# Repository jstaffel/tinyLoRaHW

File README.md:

# tinyLoRaHW
Hardware files of the tinyLoRa, a board that uses Rapsberry Pi's RP2040 microcontroller for LoRaWAN communication.
The board was designed in KiCad

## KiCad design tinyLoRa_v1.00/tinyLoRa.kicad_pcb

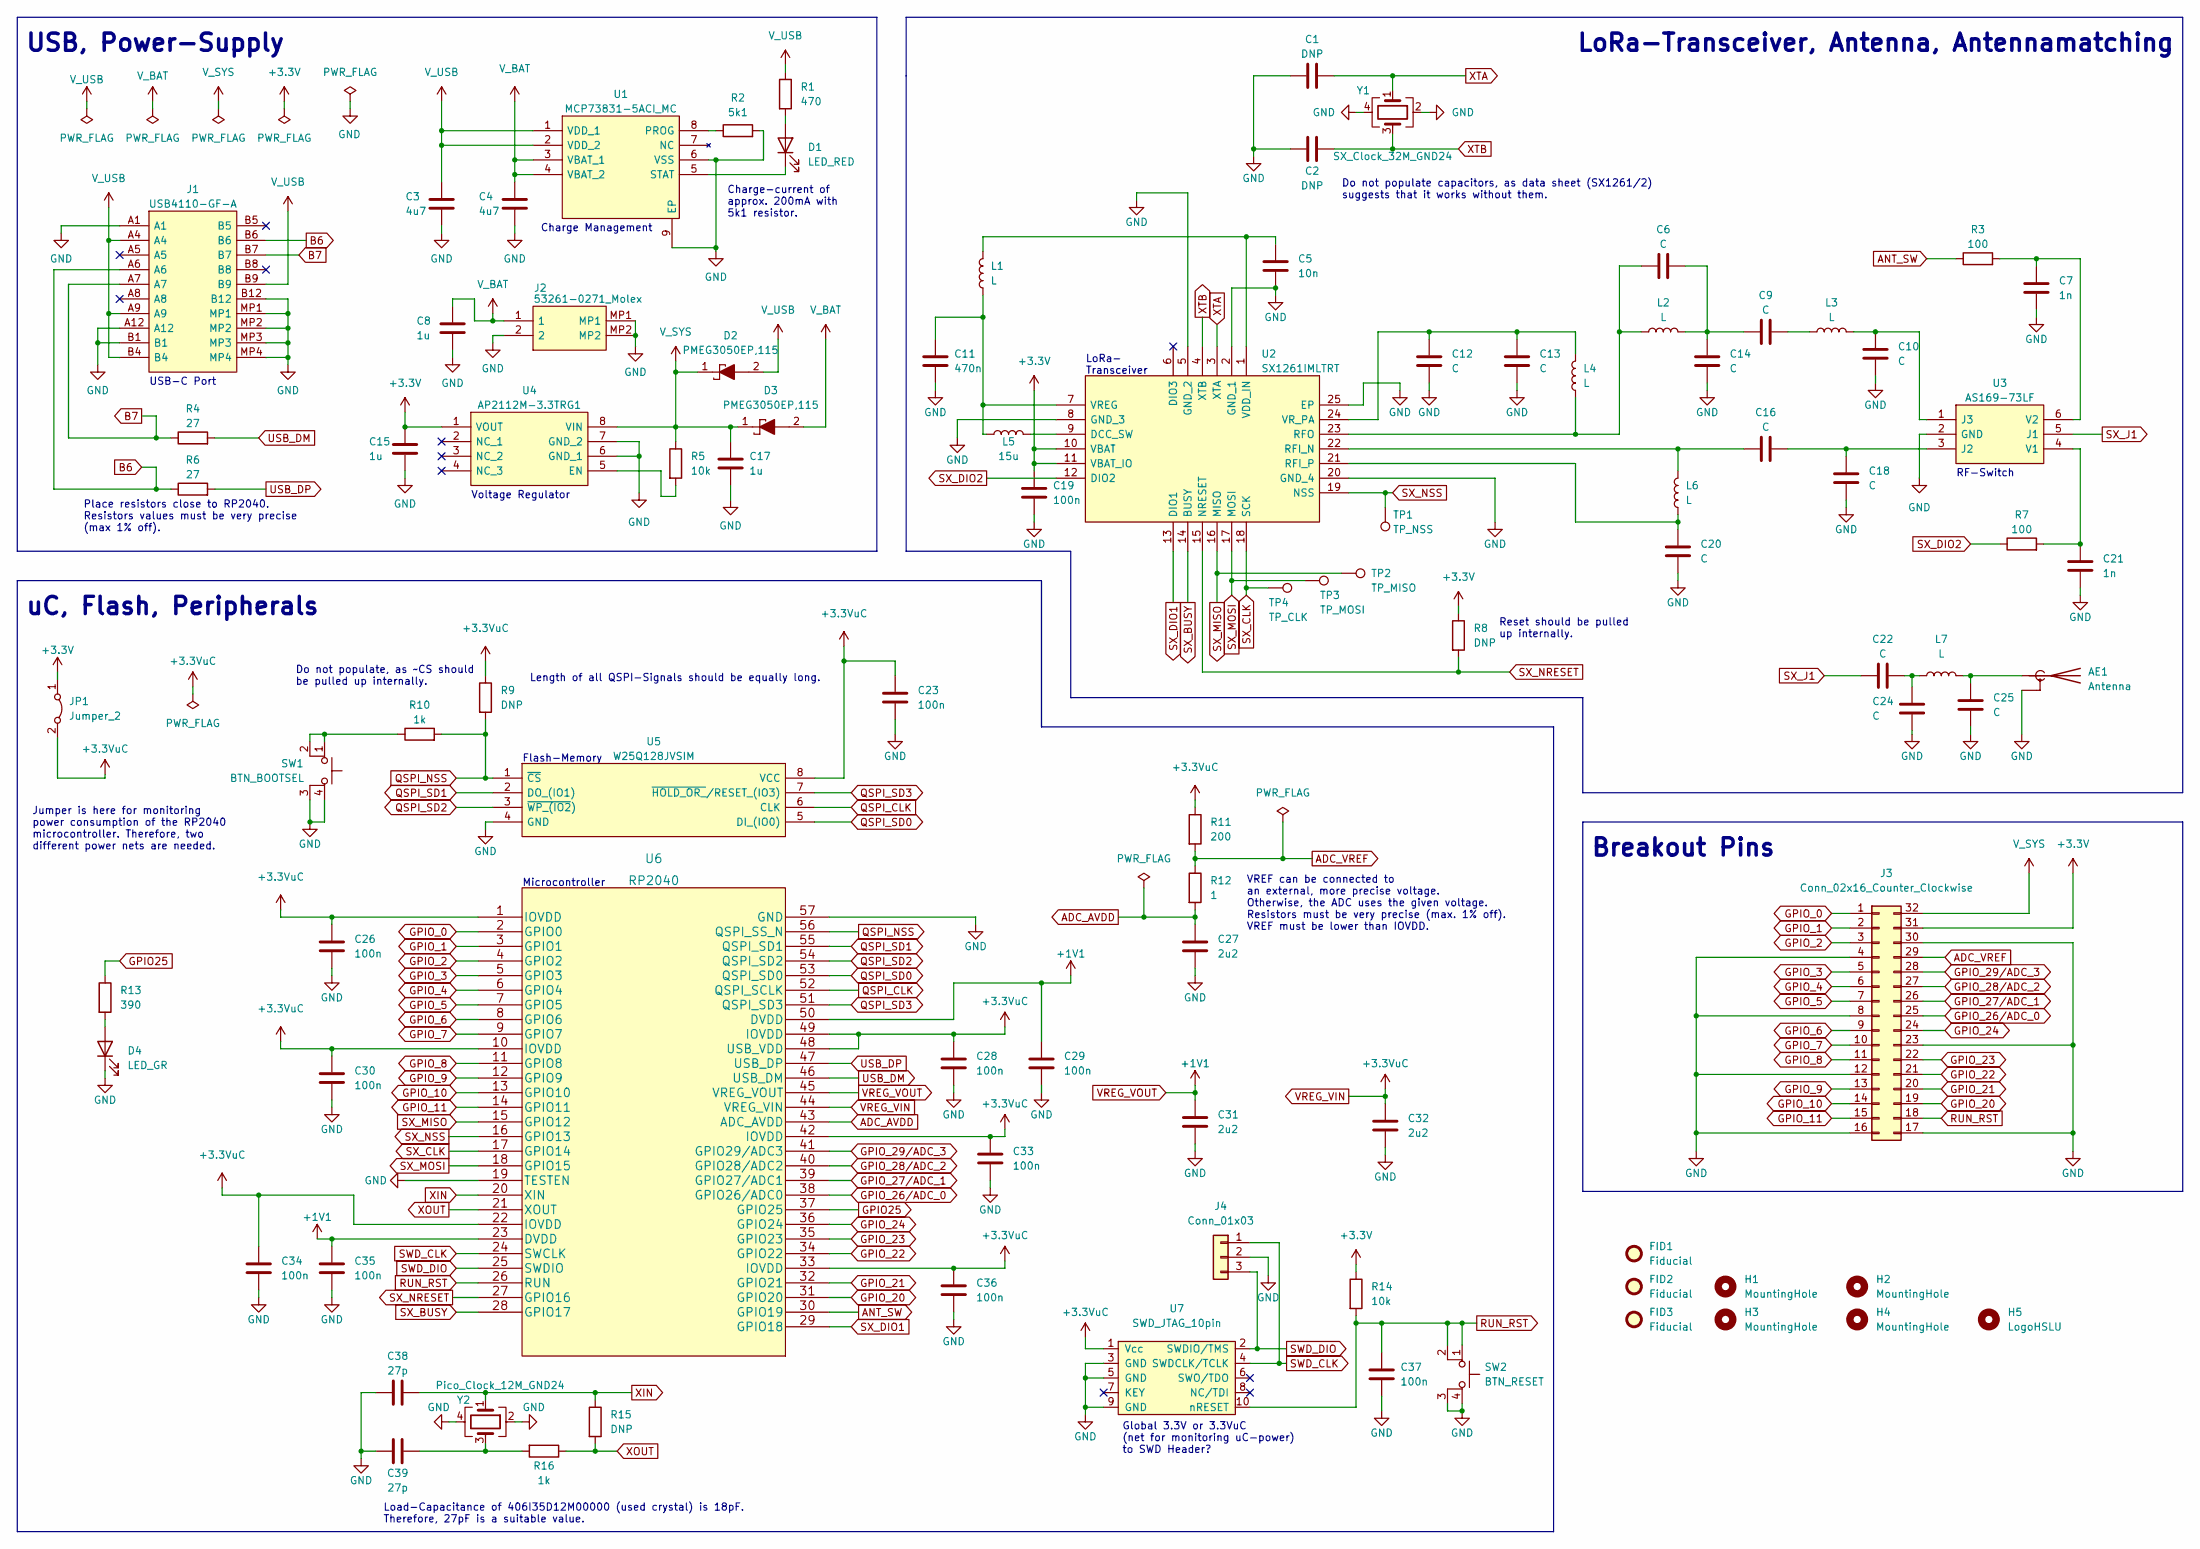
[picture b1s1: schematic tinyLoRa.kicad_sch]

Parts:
AE1: Antenna; antenna_connector
C1, C2: DNP; R_0603_1608Metric
C3, C4: 4u7; R_0603_1608Metric
C5: 10n; R_0603_1608Metric
C6, C9, C10, C12, C13, C14, C16, C18, C20, C22, C24, C25: C; R_0402_1005Metric
C7, C21: 1n; R_0603_1608Metric
C8, C15, C17: 1u; R_0603_1608Metric
C11: 470n; R_0603_1608Metric
C19, C23, C37: 100n; R_0603_1608Metric
C26, C28, C29, C30, C33, C34, C35, C36: 100n; R_0402_1005Metric
C27, C31, C32: 2u2; R_0402_1005Metric
C38, C39: 27p; R_0603_1608Metric
D1: LED_RED; R_0603_1608Metric
D2, D3: PMEG3050EP,115; PMEG3050EP115; Mouser Part Number 771-PMEG3050EP115
D4: LED_GR; R_0603_1608Metric
FID1, FID2, FID3: Fiducial; Fiducial_1mm_Dia_2.54mm_Outer_CopperTop
H1, H2, H3, H4: MountingHole; MountingHole_2.7mm_M2.5_LargeMask
H5: LogoHSLU; hslu_logo_new
J1: USB4110-GF-A; USB4110GFA; Mouser Part Number 640-USB4110-GF-A
J2: 53261-0271_Molex; 532610271_Molex; Mouser Part Number 538-53261-0271
J3: Conn_02x16_Counter_Clockwise; PinHeader_tinyLoRa
J4: Conn_01x03; PinSocket_1x03_P2.54mm_Vertical
JP1: Jumper_2; PinSocket_1x02_P2.54mm_Vertical
L1: L; R_0603_1608Metric
L2, L3, L4, L6, L7: L; R_0402_1005Metric
L5: 15u; R_0603_1608Metric
R1: 470; R_0603_1608Metric
R2: 5k1; R_0603_1608Metric
R3, R7: 100; R_0603_1608Metric
R4, R6: 27; R_0603_1608Metric
R5, R14: 10k; R_0603_1608Metric
R8, R9, R15: DNP; R_0603_1608Metric
R10, R16: 1k; R_0603_1608Metric
R11: 200; R_0603_1608Metric
R12: 1; R_0603_1608Metric
R13: 390; R_0603_1608Metric
SW1: BTN_BOOTSEL; 434123025826_BTN
SW2: BTN_RESET; 434123025826_BTN
TP1: TP_NSS; TestPoint_Pad_D1.0mm
TP2: TP_MISO; TestPoint_Pad_D1.0mm
TP3: TP_MOSI; TestPoint_Pad_D1.0mm
TP4: TP_CLK; TestPoint_Pad_D1.0mm
U1: MCP73831-5ACI_MC; SON50P300X200X100-9N-D; Mouser Part Number 579-MCP73831-5ACI/MC
U2: SX1261IMLTRT; QFN50P400X400X100-25N-D; Mouser Part Number 947-SX1261IMLTRT
U3: AS169-73LF; SOT95P270X145-6N; Mouser Part Number 873-AS169-73LF
U4: AP2112M-3.3TRG1; SOIC127P600X170-8N; Mouser Part Number 621-AP2112M-3.3TRG1
U5: W25Q128JVSIM; SOIC127P790X216-8N; Mouser Part Number 454-W25Q128JVSIM
U6: RP2040
U7: SWD_JTAG_10pin; SWD_Pin_Header_Straight_2x05_Pitch1.27mm
Y1: SX_Clock_32M_GND24; SX_Clock_GND24
Y2: Pico_Clock_12M_GND24; Pico_Clock_GND24

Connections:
+3V3: C15.1, C19.1, J3.31, JP1.1 (A), R8.1, R14.1, U2.10 (VBAT), U2.11 (VBAT_IO), U4.1 (VOUT)
ADC_AVDD: C27.1, R12.2, U6.43 (ADC_AVDD)
ADC_VREF: J3.29, R11.2, R12.1
ANT_SW: R3.1, U6.30 (GPIO19)
B6: J1.A6, J1.B6, R6.1
B7: J1.A7, J1.B7, R4.1
GND: AE1.2 (Shield), C1.1, C2.1, C3.2, C4.2, C5.2, C7.2, C8.2, C10.2, C11.2, C12.2, C13.2, C14.2, C15.2, C17.2, C18.2, C19.2, C20.2, C21.2, C23.2, C24.1, C25.1, C26.2, C27.2, C28.2, C29.2, C30.2, C31.2, C32.2, C33.2, C34.2, C35.2, C36.2, C37.2, C38.1, C39.1, D4.1 (K), J1.A1, J1.A12, J1.B1, J1.B12, J1.MP1, J1.MP2, J1.MP3, J1.MP4, J2.2, J2.MP1, J2.MP2, J3.4, J3.8, J3.12, J3.16, J3.17, J3.23, J3.30, J4.2, R2.2, SW1.3 (K), SW1.4 (A), SW2.3 (K), SW2.4 (A), U1.6 (VSS), U1.9 (EP), U2.2 (GND_1), U2.5 (GND_2), U2.8 (GND_3), U2.20 (GND_4), U2.25 (EP), U3.2 (GND), U4.6 (GND_1), U4.7 (GND_2), U5.4 (GND), U6.19 (TESTEN), U6.57 (GND), U7.3 (GND), U7.5 (GND), U7.9 (GND), Y1.2, Y1.4, Y2.2, Y2.4; also elsewhere on the board
GPIO25: R13.1, U6.37 (GPIO25)
GPIO_0: J3.1, U6.2 (GPIO0)
GPIO_1: J3.2, U6.3 (GPIO1)
GPIO_2: J3.3, U6.4 (GPIO2)
GPIO_3: J3.5, U6.5 (GPIO3)
GPIO_4: J3.6, U6.6 (GPIO4)
GPIO_5: J3.7, U6.7 (GPIO5)
GPIO_6: J3.9, U6.8 (GPIO6)
GPIO_7: J3.10, U6.9 (GPIO7)
GPIO_8: J3.11, U6.11 (GPIO8)
GPIO_9: J3.13, U6.12 (GPIO9)
GPIO_10: J3.14, U6.13 (GPIO10)
GPIO_11: J3.15, U6.14 (GPIO11)
GPIO_20: J3.19, U6.31 (GPIO20)
GPIO_21: J3.20, U6.32 (GPIO21)
GPIO_22: J3.21, U6.34 (GPIO22)
GPIO_23: J3.22, U6.35 (GPIO23)
GPIO_24: J3.24, U6.36 (GPIO24)
GPIO_26/ADC_0: J3.25, U6.38 (GPIO26/ADC0)
GPIO_27/ADC_1: J3.26, U6.39 (GPIO27/ADC1)
GPIO_28/ADC_2: J3.27, U6.40 (GPIO28/ADC2)
GPIO_29/ADC_3: J3.28, U6.41 (GPIO29/ADC3)
unnamed: AE1.1 (A), C25.2, L7.2
unnamed: C5.1, L1.2, U2.1 (VDD_IN)
unnamed: C6.1, L2.1, L4.1, U2.23 (RFO)
unnamed: C7.1, R3.2, U3.6 (V2)
unnamed: C9.2, L3.1
unnamed: C10.1, L3.2, U3.1 (J3)
unnamed: C11.1, L1.1, L5.1, U2.7 (VREG)
unnamed: C12.1, C13.1, L4.2, U2.24 (VR_PA)
unnamed: C6.2, C9.1, C14.1, L2.2
unnamed: C16.1, L6.2, U2.22 (RFI_N)
unnamed: C16.2, C18.1, U3.3 (J2)
unnamed: C20.1, L6.1, U2.21 (RFI_P)
unnamed: C21.1, R7.2, U3.4 (V1)
unnamed: C22.2, C24.2, L7.1
unnamed: C39.2, R16.2, Y2.3
unnamed 44: D1.1 (K), U1.5 (STAT); also elsewhere on the board
unnamed 45: D1.2 (A), R1.2; also elsewhere on the board
unnamed: D4.2 (A), R13.2
unnamed: L5.2, U2.9 (DCC_SW)
unnamed: R2.1, U1.8 (PROG)
unnamed: R5.2, U4.5 (EN)
unnamed 50: R10.1, SW1.1, SW1.2; also elsewhere on the board
QSPI_CLK: U5.6 (CLK), U6.52 (QSPI_SCLK)
QSPI_NSS: R9.2, R10.2, U5.1 (~CS), U6.56 (QSPI_SS_N)
QSPI_SD0: U5.5 (DI_(IO0)), U6.53 (QSPI_SD0)
QSPI_SD1: U5.2 (DO_(IO1)), U6.55 (QSPI_SD1)
QSPI_SD2: U5.3 (~WP_(IO2)), U6.54 (QSPI_SD2)
QSPI_SD3: U5.7 (~HOLD_OR_/RESET_(IO3)), U6.51 (QSPI_SD3)
RUN_RST: C37.1, J3.18, R14.2, SW2.1, SW2.2, U6.26 (RUN), U7.10 (nRESET); also elsewhere on the board
SWD_CLK: J4.1, U6.24 (SWCLK), U7.4 (SWDCLK/TCLK)
SWD_DIO: J4.3, U6.25 (SWDIO), U7.2 (SWDIO/TMS)
SX_BUSY: U2.14 (BUSY), U6.28 (GPIO17)
SX_CLK: TP4.1, U2.18 (SCK), U6.17 (GPIO14)
SX_DIO1: U2.13 (DIO1), U6.29 (GPIO18)
SX_DIO2: R7.1, U2.12 (DIO2)
SX_J1: C22.1, U3.5 (J1)
SX_MISO: TP2.1, U2.16 (MISO), U6.15 (GPIO12)
SX_MOSI: TP3.1, U2.17 (MOSI), U6.18 (GPIO15)
SX_NRESET: R8.2, U2.15 (NRESET), U6.27 (GPIO16)
SX_NSS: TP1.1, U2.19 (NSS), U6.16 (GPIO13)
USB_DM: R4.2, U6.46 (USB_DM)
USB_DP: R6.2, U6.47 (USB_DP)
VREG_VIN: C23.1, C26.1, C28.1, C30.1, C32.1, C33.1, C34.1, C36.1, JP1.2 (B), R9.1, R11.1, U5.8 (VCC), U6.1 (IOVDD), U6.10 (IOVDD), U6.22 (IOVDD), U6.33 (IOVDD), U6.42 (IOVDD), U6.44 (VREG_VIN), U6.48 (USB_VDD), U6.49 (IOVDD), U7.1 (Vcc)
VREG_VOUT: C29.1, C31.1, C35.1, U6.23 (DVDD), U6.45 (VREG_VOUT), U6.50 (DVDD)
V_BAT: C4.1, C8.1, D3.2, J2.1, U1.3 (VBAT_1), U1.4 (VBAT_2)
V_SUB: C3.1, D2.2, J1.A4, J1.A9, J1.B4, J1.B9, R1.1, U1.1 (VDD_1), U1.2 (VDD_2)
V_SYS: C17.1, D2.1, D3.1, J3.32, R5.1, U4.8 (VIN)
XIN: C38.2, R15.1, U6.20 (XIN), Y2.1
XOUT: R15.2, R16.1, U6.21 (XOUT)
XTA: C1.2, U2.3 (XTA), Y1.1
XTB: C2.2, U2.4 (XTB), Y1.3

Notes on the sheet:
RF-Switch
LoRa-Transceiver, Antenna, Antennamatching
LoRa- Transceiver
USB-C Port
Global 3.3V or 3.3VuC (net for monitoring uC-power) to SWD Header?
Do not populate, as ~CS should be pulled up internally.
Length of all QSPI-Signals should be equally long.
Charge-current of approx. 200mA with 5k1 resistor.
Do not populate capacitors, as data sheet (SX1261/2) suggests that it works without them.
Voltage Regulator
USB, Power-Supply
Charge Management
Load-Capacitance of 406I35D12M00000 (used crystal) is 18pF. Therefore, 27pF is a suitable value.
Jumper is here for monitoring power consumption of the RP2040 microcontroller. Therefore, two different power nets are needed.
uC, Flash, Peripherals
VREF can be connected to an external, more precise voltage. Otherwise, the ADC uses the given voltage. Resistors must be very precise (max. 1% off). VREF must be lower than IOVDD.
Place resistors close to RP2040. Resistors values must be very precise (max 1% off).
Microcontroller
Flash-Memory
Reset should be pulled up internally.
Breakout Pins

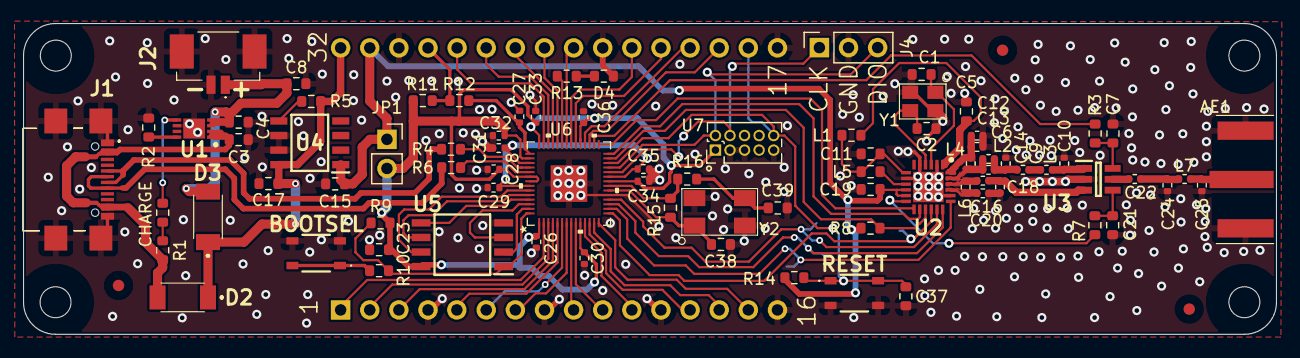
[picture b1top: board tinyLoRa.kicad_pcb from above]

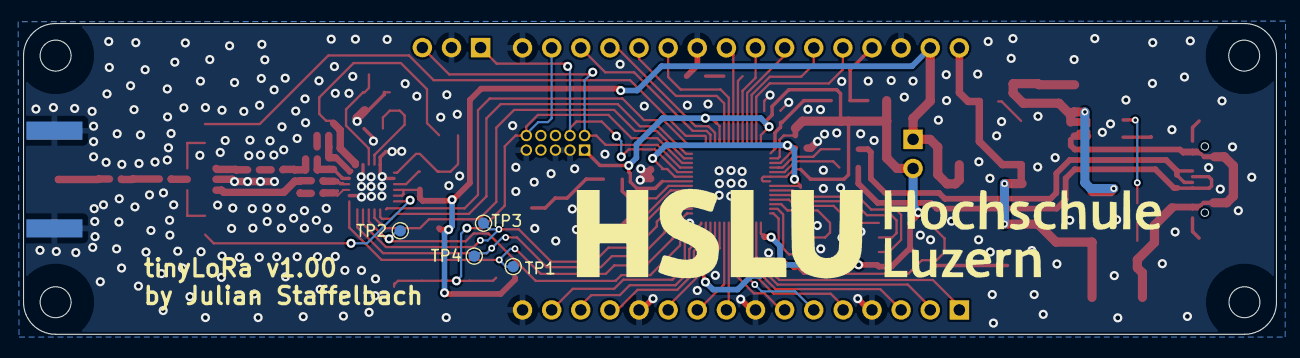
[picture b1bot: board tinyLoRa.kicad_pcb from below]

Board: 2 copper layers, 109.3 x 27.1 mm, 95 parts (5 on the bottom side), 80 nets.

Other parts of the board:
BOOTSEL: BTN_BOOTSEL; 434123025826_BTN
CHARGE: LED_RED; R_0603_1608Metric
RESET: BTN_RESET; 434123025826_BTN

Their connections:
GND: BOOTSEL.3 (K), BOOTSEL.4 (A), RESET.3 (K), RESET.4 (A); also elsewhere on the board
unnamed 44: CHARGE.1 (K); also elsewhere on the board
unnamed 45: CHARGE.2 (A); also elsewhere on the board
unnamed 50: BOOTSEL.1, BOOTSEL.2; also elsewhere on the board
RUN_RST: RESET.1, RESET.2; also elsewhere on the board

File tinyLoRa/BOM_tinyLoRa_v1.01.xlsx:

tinyLoRa |  |  | BOM |  |  | v1.01
 |  |  |  |  |  | 44718
RefDes | MPN | Geometry | Value | Qty | Description | Manufacturer
IC
U1 | MCP73831-5ACI_MC | - | - | 1 | Battery Management Li-Ion/Li-Poly Charg Mgnt 4.5V Vreg out | Microchip
U2 | SX1261IMLTRT | - | - | 1 | RF Transceiver LoRa, Low Power sub- GHz RF Transceiver | SEMTECH
U3 | AS213-92LF | - | - | 1 | SKYWORKS SOLUTIONS - AS213-92LF - IC, SWITCH, RF, SPDT, 0.1-3.0GHZ | Skyworks
U4 | AP2112M-3.3TRG1 | - | - | 1 | LDO Voltage Regulators LDO CMOS HiCurr | Diodes Inc.
U5 | W25Q128JVSIM | - | - | 1 | NOR-Flash spiFlash, 3V, 128M-bit, 4Kb Uniform Sector, DTR | Winbond
U6 | RPI Chip RP2040-7-500 | - | - | 1 | Dual ARM Cortex M0+ Microcontroller | Raspberry Pi
Resistors
R1 | - | 0603_1608 | 470 | 1 | - | -
R2 | - | 0603_1608 | 5k1 | 1 | - | -
R3 | - | 0603_1608 | 100 | 1 | - | -
R4 | CMP0603AFX-27R0ELF | 0603_1608 | 27 | 1 | Thick Film Resistors ResHighPowerA 0603 27R 1% 1/4W TC100 | Bourns
R5 | - | 0603_1608 | 10k | 1 | - | -
R6 | CMP0603AFX-27R0ELF | 0603_1608 | 27 | 1 | Thick Film Resistors ResHighPowerA 0603 27R 1% 1/4W TC100 | Bourns
R7 | - | 0603_1608 | 100 | 1 | - | -
R8 | - | 0603_1608 | DNP | 1 | - | -
R9 | - | 0603_1608 | DNP | 1 | - | -
R10 | - | 0603_1608 | 1k | 1 | - | -
R11 | ERJ-UP3F2000V | 0603_1608 | 200 | 1 | Thick Film Resistors 0603 0.25W 1% 200ohm AEC-Q200 | Panasonic
R12 | ERJ-U03F1R00V | 0603_1608 | 1 | 1 | Thick Film Resistors 0603 1% 1ohm AEC-Q200 Anti-Sulfur | Panasonic
R13 | - | 0603_1608 | 390 | 1 | - | -
R14 | - | 0603_1608 | 10k | 1 | - | -
R15 | - | 0603_1608 | DNP | 1 | - | -
R16 | - | 0603_1608 | 1k | 1 | - | -
Capacitors
C1 | - | 0603_1608 | DNP | 1 | - | -
C2 | - | 0603_1608 | DNP | 1 | - | -
C3 | ZRB18AR6YA475KE05L | 0603_1608 | 4u7 | 1 | Multilayer Ceramic Capacitors MLCC - SMD/SMT | Murata Electronics
C4 | ZRB18AR6YA475KE05L | 0603_1608 | 4u7 | 1 | Multilayer Ceramic Capacitors MLCC - SMD/SMT | Murata Electronics
C5 | - | 0603_1608 | 10n | 1 | - | -
C6 | GRM1555C1H3R0BA01D | 0402_1005 | 3p | 1 | Multilayer Ceramic Capacitors MLCC - SMD/SMT | Murata Electronics
C7 | - | 0603_1608 | 1n | 1 | - | -
C8 | - | 0603_1608 | 1u | 1 | - | -
C9 | GRM1555C1H120JA01J | 0402_1005 | 12p | 1 | Multilayer Ceramic Capacitors MLCC - SMD/SMT | Murata Electronics
C10 | UVK105CH2R2JW-F | 0402_1005 | 2p2 | 1 | Multilayer Ceramic Capacitors MLCC - SMD/SMT | Taiyo Yuden
C11 | GCJ188R71C474KA12D | 0603_1608 | 470n | 1 | Multilayer Ceramic Capacitors MLCC - SMD/SMT | Murata Electronics
C12 | GRM155C71H473JE19D | 0402_1005 | 47n | 1 | Multilayer Ceramic Capacitors MLCC - SMD/SMT | Murata Electronics
C13 | GCM1555C1H470JA16J | 0402_1005 | 47p | 1 | Multilayer Ceramic Capacitors MLCC - SMD/SMT | Murata Electronics
C14 | C0402C569J5GACTU | 0402_1005 | 5p6 | 1 | Multilayer Ceramic Capacitors MLCC - SMD/SMT | KEMET
C15 | - | 0603_1608 | 1u | 1 | - | -
C16 | GRM1555C1H1R8WA01D | 0402_1005 | 1p8 | 1 | Multilayer Ceramic Capacitors MLCC - SMD/SMT | Murata Electronics
C17 | - | 0603_1608 | 1u | 1 | - | -
C18 | GRM1555C1H1R0BA01D | 0402_1005 | 1p | 1 | Multilayer Ceramic Capacitors MLCC - SMD/SMT | Murata Electronics
C19 | - | 0603_1608 | 100n | 1 | - | -
C20 | GRM1555C1H1R8WA01D | 0402_1005 | 1p8 | 1 | Multilayer Ceramic Capacitors MLCC - SMD/SMT | Murata Electronics
C21 | - | 0603_1608 | 1n | 1 | - | -
C22 | GRM1555C1H220JA01D | 0402_1005 | 22p | 1 | Multilayer Ceramic Capacitors MLCC - SMD/SMT | Murata Electronics
C23 | - | 0603_1608 | 100n | 1 | - | -
C24 | UVK105CG3R3JW-F | 0402_1005 | 3p3 | 1 | Multilayer Ceramic Capacitors MLCC - SMD/SMT | Taiyo Yuden
C25 | UVK105CG3R3JW-F | 0402_1005 | 3p3 | 1 | Multilayer Ceramic Capacitors MLCC - SMD/SMT | Taiyo Yuden
C26 | CGA2B1X7R1C104K050BC | 0402_1005 | 100n | 1 | Multilayer Ceramic Capacitors MLCC - SMD/SMT CGA | TDK
C27 | C1005X5R1V225K050BE | 0402_1005 | 2u2 | 1 | Multilayer Ceramic Capacitors MLCC - SMD/SMT | TDK
C28 | CGA2B1X7R1C104K050BC | 0402_1005 | 100n | 1 | Multilayer Ceramic Capacitors MLCC - SMD/SMT CGA | TDK
C29 | CGA2B1X7R1C104K050BC | 0402_1005 | 100n | 1 | Multilayer Ceramic Capacitors MLCC - SMD/SMT CGA | TDK
C30 | CGA2B1X7R1C104K050BC | 0402_1005 | 100n | 1 | Multilayer Ceramic Capacitors MLCC - SMD/SMT CGA | TDK
C31 | C1005X5R1V225K050BE | 0402_1005 | 2u2 | 1 | Multilayer Ceramic Capacitors MLCC - SMD/SMT | TDK
C32 | C1005X5R1V225K050BE | 0402_1005 | 2u2 | 1 | Multilayer Ceramic Capacitors MLCC - SMD/SMT | TDK
C33 | CGA2B1X7R1C104K050BC | 0402_1005 | 100n | 1 | Multilayer Ceramic Capacitors MLCC - SMD/SMT CGA | TDK
C34 | CGA2B1X7R1C104K050BC | 0402_1005 | 100n | 1 | Multilayer Ceramic Capacitors MLCC - SMD/SMT CGA | TDK
C35 | CGA2B1X7R1C104K050BC | 0402_1005 | 100n | 1 | Multilayer Ceramic Capacitors MLCC - SMD/SMT CGA | TDK
C36 | CGA2B1X7R1C104K050BC | 0402_1005 | 100n | 1 | Multilayer Ceramic Capacitors MLCC - SMD/SMT CGA | TDK
C37 | - | 0603_1608 | 100n | 1 | - | -
C38 | GRM1885C2E270JW07D | 0603_1608 | 27p | 1 | Multilayer Ceramic Capacitors MLCC - SMD/SMT | Murata Electronics
C39 | GRM1885C2E270JW07D | 0603_1608 | 27p | 1 | Multilayer Ceramic Capacitors MLCC - SMD/SMT | Murata Electronics
Inductors
L1 | LQG15WZ47NH02D | 0402_1005 | 47n | 1 | Fixed Inductors Fixed IND 47nH 190mA | Murata Electronics
L2 | LQW15AN2N7C00D | 0402_1005 | 2n7 | 1 | Fixed Inductors 2.7 NH +-.2NH | Murata Electronics
L3 | LQP15MN9N1B02D | 0402_1005 | 9n1 | 1 | Fixed Inductors | Murata Electronics
L4 | LQG15WZ47NH02D | 0402_1005 | 47n | 1 | Fixed Inductors Fixed IND 47nH 190mA | Murata Electronics
L5 | LQM18DN150M70L | 0603_1608 | 15u | 1 | Fixed Inductors | Murata Electronics
L6 | LQW15AN18NH00D | 0402_1005 | 18n | 1 | Fixed Inductors 18 NH 3% | Murata Electronics
L7 | LQP15MN9N1B02D | 0402_1005 | 9n1 | 1 | Fixed Inductors | Murata Electronics
Diodes & LEDs
D1 | XZMDK53W-8 | 0603_1608 | LED Red | 1 | LED RED CLEAR CHIP SMD | SunLED
D2 | PMEG3050EP,115 | 2.7 x 4 mm | - | 1 | SMT Schottky Diode, 30V 5A, 2-Pin SOD-128 | Nexperia
D3 | PMEG3050EP,115 | 2.7 x 4 mm | - | 1 | SMT Schottky Diode, 30V 5A, 2-Pin SOD-128 | Nexperia
D4 | XZVG53W-8 | 0603_1608 | LED Green | 1 | LED GREEN CLEAR CHIP SMD | SunLED
Crystals
Y1 | LFXTAL060258Reel | 2.7 x 3.4 mm | 32.0 MHz | 1 | Crystals 32MHz 10pF -20C 70C | IQD
Y2 | 406I35D12M00000 | 3.5 x 6 mm | 12.0 MHz | 1 | Crystals 12MHz 30ppm 18pF -40C + 85C | CTS Electronic Components
Connectors, Buttons & other
AE1 | CONSMA020.042-G | 14.2 x 9.5 x 7.9 mm | - | 1 | RF Connectors SMA Connector Straight Jack (Female), PCB Edge Mount | Linx Technologies
J1 | USB4110-GF-A | 10.2 x 7.7 mm | USB-C | 1 | CONN USB 2.0 TYPE-C R/A SMT | GCT
J2 | 53261-0271 | 1.25 mm | 1X2 | 1 | Headers & Wire Housings 1.25MM HDR 2 CKT Right-Angle | Molex
J3 | - | 2.54 mm | 2x16 | 1 | Pin-Header male 2.54 mm | -
J4 | - | 2.54 mm | 1x3 | 1 | Pin-Header female 2.54 mm | -
JP1 | - | 2.54 mm | 1x2 | 1 | Pin-Header male 2.54 mm | -
U7 | - | 1.27 mm | 2x5 | 1 | Pin-Header male 1.27 mm | -
SW1 | 434123025826 | 2.8 x 5.2 mm | Bootsel | 1 | WS-TASV J-Bend SMT Tact Switch | Würth Elektronik
SW2 | 434123025826 | 2.8 x 5.2 mm | Reset | 1 | WS-TASV J-Bend SMT Tact Switch | Würth Elektronik

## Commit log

2022-07-30 copy in this repo

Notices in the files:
parts and their libraries:
Copyright 2021 Accelerated Designs. All rights reserved.
